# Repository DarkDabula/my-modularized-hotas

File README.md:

# My Modularized HOTAS
A modularized, mostly 3D printed HOTAS with HID emulation via Arduino

## Motivation
On Christmas 2020 I stumbled over [Elite Dangerous](https://www.elitedangerous.com/) and got hooked. After a while I began to play it in VR.
At this point I realized I would need a HOTAS system. The problem was that through the pademic all systems were mostly sold out. 
I had already a joystick so I built a throttle lever made of metal parts, wood and some electronics. And it served me pretty well.

But after hundreds of hours I recognized that the simple push buttons got weak and that I would need more buttons for effective playing in VR.
In 2021 I bought a 3D printer and the idea was born to contruct a new and better throttle lever and maybe after this a new joystick.

## Goals
- As much 3D printed parts as possible and reasonable
- Modularized design for easy printing, assembly, customization and repair

## Current state
See [here](./status.md)

## Concepts
See [here](./concepts.md)

## External parts
For this project additional parts/components are needed besides the 3D printed ones.

| ID     | Ammount   | Item                   | Picture                             | Example link for buying                                                                                                   |
|----------|---------|------------------------|-------------------------------------|---------------------------------------------------------------------------------------------------------------------------|
| CON3     |      3  | Connector 3 pins       |  | |
| CON5     |      1  | Connector 5 pins       | | |
| MS       |      4  | Micro swith            |  | [Link](https://www.ebay.com/sch/i.html?_from=R40&_trksid=p2380057.m570.l1313&_nkw=micro+limit+switch+125V+1A&_sacat=0) | 
| PB       |     10  | Push button            |   | [Link](https://www.ebay.com/sch/i.html?_from=R40&_trksid=p2380057.m570.l1313&_nkw=micro+button+7mm+non+latching&_sacat=0) |
| SC25     |      4  | Screw 2,5x13 (metric)  |  | |
| SCM3     |      1  | Screw M3x20 (metric)   |  | |
| SC35_7   |      1  | Screw 3,5x7 (metric)   |  | |
| SC35_95  |      4  | Screw 3,5x9,5 (metric) |  | |
| SCM4_10  |      8  | Screw M4x10 (metric)   |  | |
| SCM4_20  |      2  | Screw M4x20 (metric)   |  | |
| SCN4     |      2  | Stop nut M4 (metric)   |  | |

## Toolchain
- [FreeCAD](https://www.freecad.org/) 0.19
- [Cura](https://ultimaker.com/software/ultimaker-cura) 4.12.1 (or above)
- [Creality Ender 6](https://www.creality.com/goods-detail/ender-6-3d-printer) (modified)
- [Arduino IDE](https://www.arduino.cc/en/software)
- [KiCad](https://www.kicad.org/)

## License
This projects is licensed under the terms of [CC BY-NC 4.0](https://creativecommons.org/licenses/by-nc/4.0/)

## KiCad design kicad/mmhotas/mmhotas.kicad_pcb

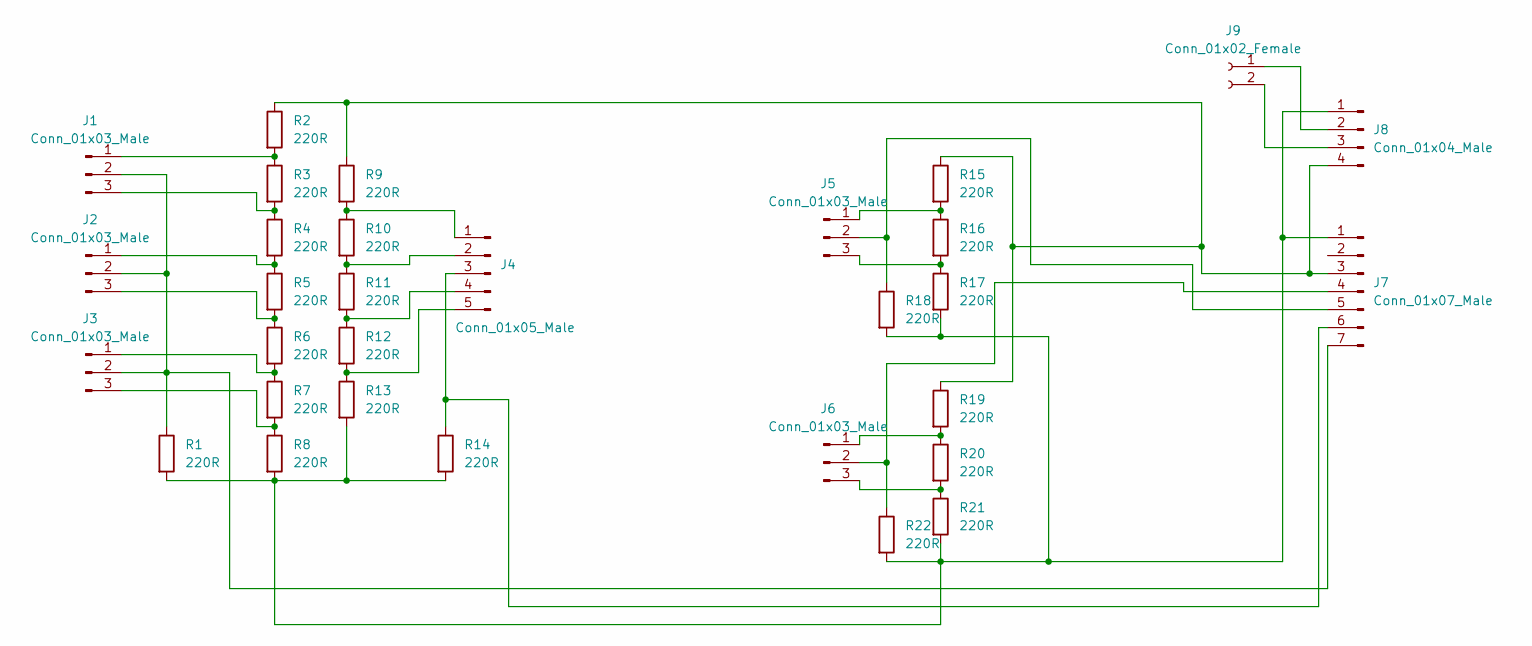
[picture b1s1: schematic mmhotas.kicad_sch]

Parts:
J1, J2, J3, J5, J6: Conn_01x03_Male; JST_XH_B3B-XH-A_1x03_P2.50mm_Vertical
J4: Conn_01x05_Male; JST_XH_B5B-XH-A_1x05_P2.50mm_Vertical
J7: Conn_01x07_Male; PinHeader_1x07_P2.54mm_Vertical
J8: Conn_01x04_Male; PinHeader_1x04_P2.54mm_Horizontal
J9: Conn_01x02_Female; PinSocket_1x02_P2.54mm_Vertical
R1, R2, R3, R4, R5, R6, R7, R8, R9, R10, R11, R12, R13, R14, R15, R16, R17, R18, R19, R20, R21, R22: 220R; R_1206_3216Metric

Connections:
unnamed: J1.1, R2.2, R3.1
unnamed: J1.2, J2.2, J3.2, J7.7, R1.1
unnamed: J1.3, R3.2, R4.1
unnamed: J2.1, R4.2, R5.1
unnamed: J2.3, R5.2, R6.1
unnamed: J3.1, R6.2, R7.1
unnamed: J3.3, R7.2, R8.1
unnamed: J4.1, R9.2, R10.1
unnamed: J4.2, R10.2, R11.1
unnamed: J4.3, J7.6, R14.1
unnamed: J4.4, R11.2, R12.1
unnamed: J4.5, R12.2, R13.1
unnamed: J5.1, R15.2, R16.1
unnamed: J5.2, J7.5, R18.1
unnamed: J5.3, R16.2, R17.1
unnamed: J6.1, R19.2, R20.1
unnamed: J6.2, J7.4, R22.1
unnamed: J6.3, R20.2, R21.1
unnamed: J7.1, J8.1, R1.2, R8.2, R13.2, R14.2, R17.2, R18.2, R21.2, R22.2
unnamed: J7.3, J8.4, R2.1, R9.1, R15.1, R19.1
unnamed: J8.2, J9.1
unnamed: J8.3, J9.2

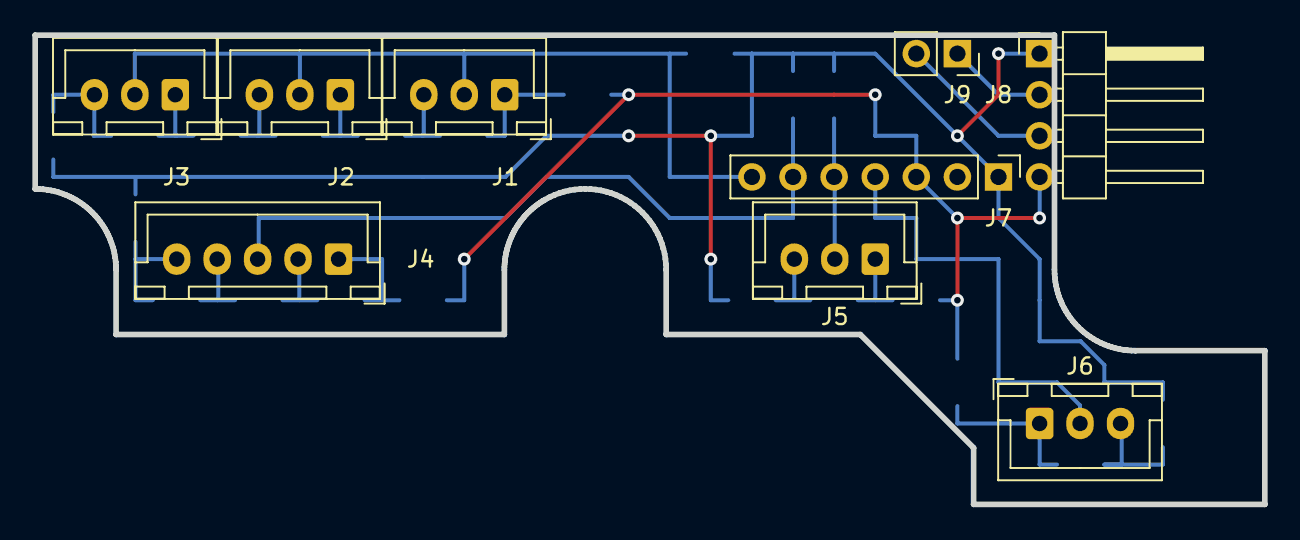
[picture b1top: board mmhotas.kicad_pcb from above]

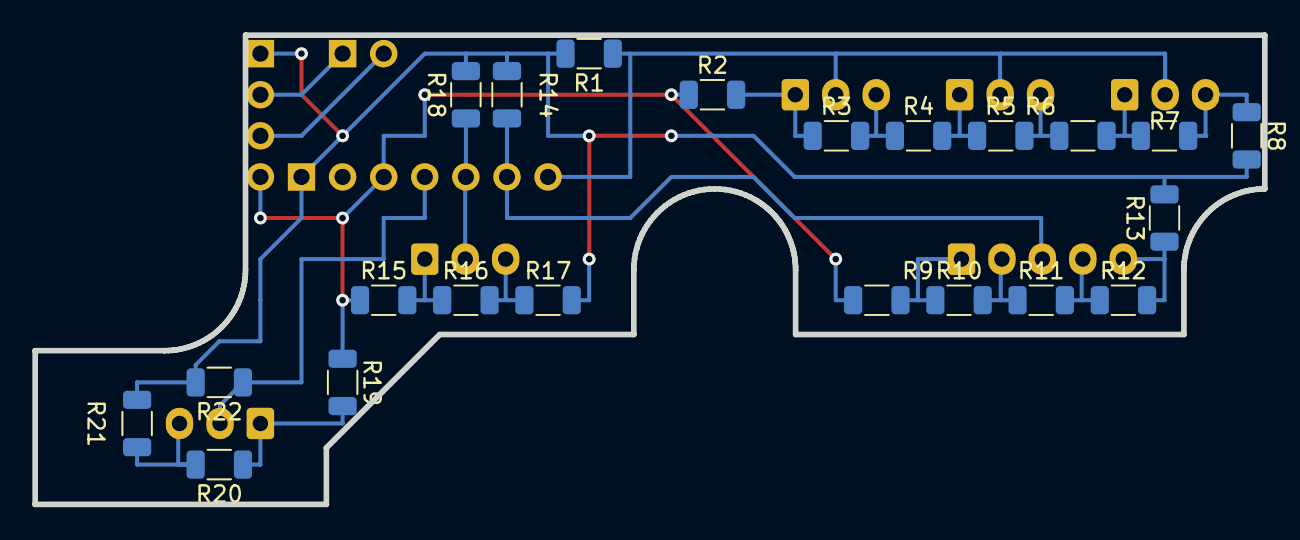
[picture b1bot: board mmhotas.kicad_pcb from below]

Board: 2 copper layers, 76.0 x 29.0 mm, 31 parts (22 on the bottom side), 22 nets.

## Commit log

2022-01-14 Delete LICENSE
    Was the wrong one
2022-01-14 Update README.md
    First real content
2022-01-14 Added folder for images and added image of prototype
2022-01-14 Added image to project description
2022-01-14 Update README.md
    Removed typo
2022-01-14 Added empty subpages
2022-01-14 Update README.md
    Slight reorg and added link to concepts
2022-01-14 Update README.md
    Added link to Arduino IDE
2022-01-14 Added image of first rocker switch
2022-01-14 Cropped and scaled image
2022-01-14 Update status.md
    First entry in diary
2022-01-14 Update README.md
    Changed title
2022-01-14 Added actual STL files for rocker module parts
2022-01-14 Update concepts.md
    First thoughts and concepts
2022-01-14 Update concepts.md
    Corrected captions
2022-01-19 Slight chages of start page
2022-01-20 Revision 1 of rocker module
2022-01-31 Added new entry, corrected wrong dates, new picture
2022-01-31 Added new status entry, corrected dates, added picture
2022-01-31 Update status.md
    Broken layout
2022-01-31 Update status.md
    Another try to fix layout
2022-02-06 Entry for the new base plate
2022-02-06 Update status.md
    Fixed image layout
2022-02-06 Fixed typo
2022-02-08 First version of baseplate
2022-06-06 - New baseplate prototype
2022-06-06 Update status.md
    Removed typo in image reference.
2022-08-07 Update README.md
    Added hint to used Cura version
2022-08-07 Documented basejoint prototype
2022-08-11 - New parts printed - Some images resized
2022-08-20 - Added images - Added links for external parts - Added FreeCAD file
2022-08-20 - Typo
2022-08-20 - Added image for switch
2022-09-25 Protottype for HAT module
2022-09-25 Fixed typos
2022-09-26 Added micro switch to parts list
2022-09-26 Button panel and button cap prototype
2022-09-26 Fixed image link
2022-09-27 Progress at right panel
2022-09-29 Created HAT für richt panel
2022-10-01 Updated part list
2022-10-03 Updates parts list
2022-10-03 Changed parts ID
2022-10-03 Updated status
2022-10-08 New rocker module
2022-10-18 Printed lever hull
2022-10-20 Lever body finished
2022-10-26 Designed connector boards
2022-10-26 Fixed link typo
2022-10-26 Fixed wrong image link
2022-11-04 Designed connector board Backups removed
2022-11-04 Designed placeholder for connector board and Arduino
2022-11-04 Sketch for slave Arduino
2022-11-04 Actual state 4th November
2022-11-12 New images
2022-11-12 Added remarks to picture
2022-11-12 New state on 11th November
2022-11-12 Removed typo
2022-11-12 Fixed more typos :)
2022-11-14 Actual source code
2022-11-14 Actual state on 14th November
2022-11-17 Added debug output for I2C
2022-11-17 Fixed wrond values if analogue value doesn't match table entry
2022-11-17 Added additional parts
2022-11-17 New images of front board
2022-11-17 Actual state on 17th November
2022-11-18 Redesigned plate magnet mount
2022-11-20 Removed old file
2022-11-20 Rework of throttle translation, more debug message
2022-11-20 Actual state on 20th November
2022-12-23 Modifications to compensate defected buttons
2022-12-23 Added cable and mount preparing new lever joint
2022-12-23 Actual state fixing a lot of typos
2023-02-05 Actual state and new Cherry switches
2023-03-06 - New redesigned lever body with Cherry switches
2023-03-06 - Corrected typo
2023-04-24 - Finished new lever head
2023-06-28 - New base plate
2023-08-01 - New lever joint
